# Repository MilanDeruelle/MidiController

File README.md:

# MidiController
Modular Midi Controller/Multiplexer Boards, Software and 3D Printed Case

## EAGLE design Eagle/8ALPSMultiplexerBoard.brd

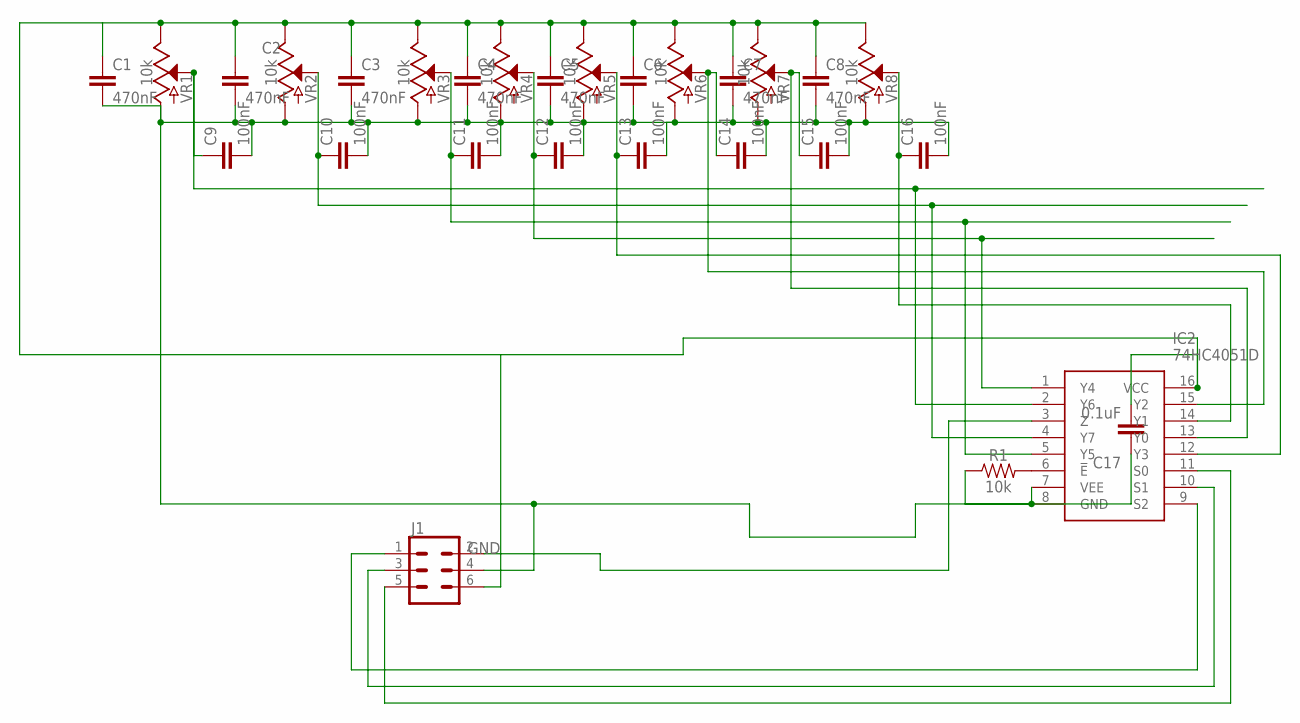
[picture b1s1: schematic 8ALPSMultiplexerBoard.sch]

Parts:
C1, C2, C3, C4, C5, C7, C8: 470nF; C0805
C6: C-EUC0805; C0805
C9, C10, C11, C12, C13, C14, C15, C16: 100nF; C0805
C17: 0.1uF; C0805
IC2: 74HC4051D; SOIC127P600X175-16N
J1: CONN_03X2FEMALE; 2X3
R1: 10k; 0805
VR1, VR2, VR3, VR4, VR5, VR6, VR7, VR8: 10k; POT-PTH-ALPS

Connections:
GND: C1.2, C2.2, C3.2, C4.2, C5.2, C6.2, C7.2, C8.2, C9.2, C10.2, C11.2, C12.2, C13.2, C14.2, C15.2, C16.2, C17.1, IC2.7 (VEE), IC2.8 (GND), J1.4, R1.1, VR1.P$3 (A), VR2.P$3 (A), VR3.P$3 (A), VR4.P$3 (A), VR5.P$3 (A), VR6.P$3 (A), VR7.P$3 (A), VR8.P$3 (A)
unnamed: IC2.6 (!E), R1.2
S0: IC2.11 (S0), J1.5
S1: IC2.10 (S1), J1.3
S2: IC2.9 (S2), J1.1
VCC: C1.1, C2.1, C3.1, C4.1, C5.1, C6.1, C7.1, C8.1, C17.2, IC2.16 (VCC), J1.6, VR1.P$1 (E), VR2.P$1 (E), VR3.P$1 (E), VR4.P$1 (E), VR5.P$1 (E), VR6.P$1 (E), VR7.P$1 (E), VR8.P$1 (E)
Y0: C9.1, IC2.2 (Y6), VR1.P$2 (S)
Y1: C10.1, IC2.4 (Y7), VR2.P$2 (S)
Y2: C11.1, IC2.5 (Y5), VR3.P$2 (S)
Y3: C12.1, IC2.1 (Y4), VR4.P$2 (S)
Y4: C13.1, IC2.12 (Y3), VR5.P$2 (S)
Y5: C14.1, IC2.15 (Y2), VR6.P$2 (S)
Y6: C15.1, IC2.13 (Y0), VR7.P$2 (S)
Y7: C16.1, IC2.14 (Y1), VR8.P$2 (S)
Z: IC2.3 (Z), J1.2

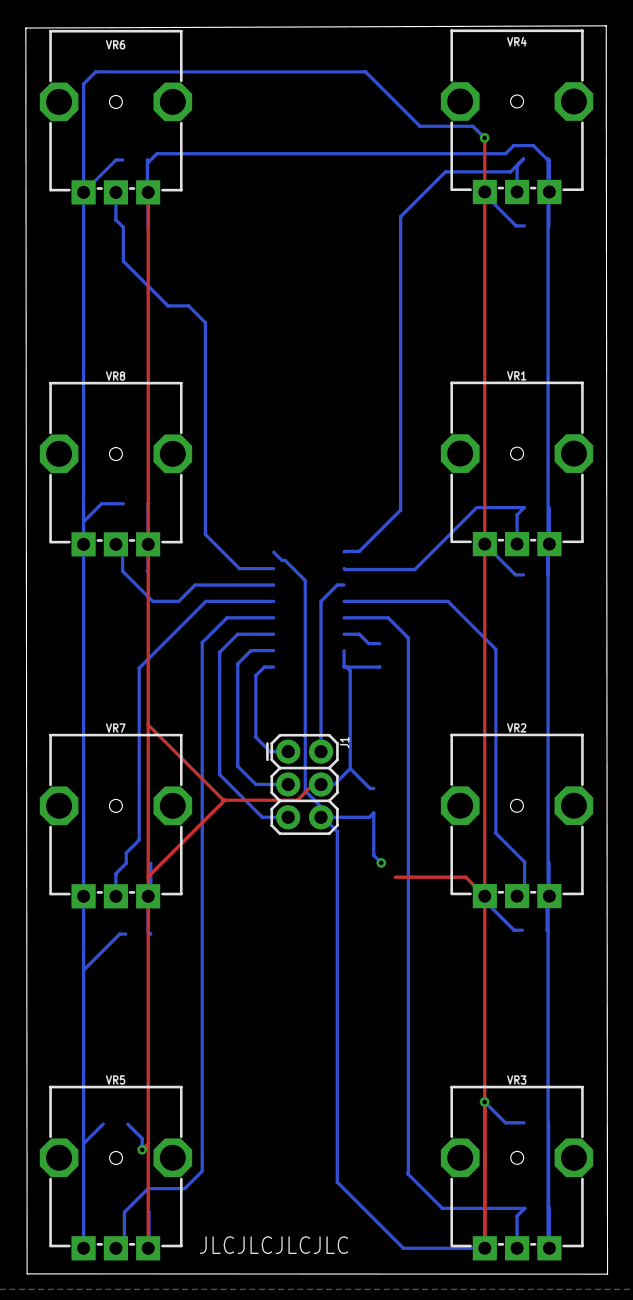
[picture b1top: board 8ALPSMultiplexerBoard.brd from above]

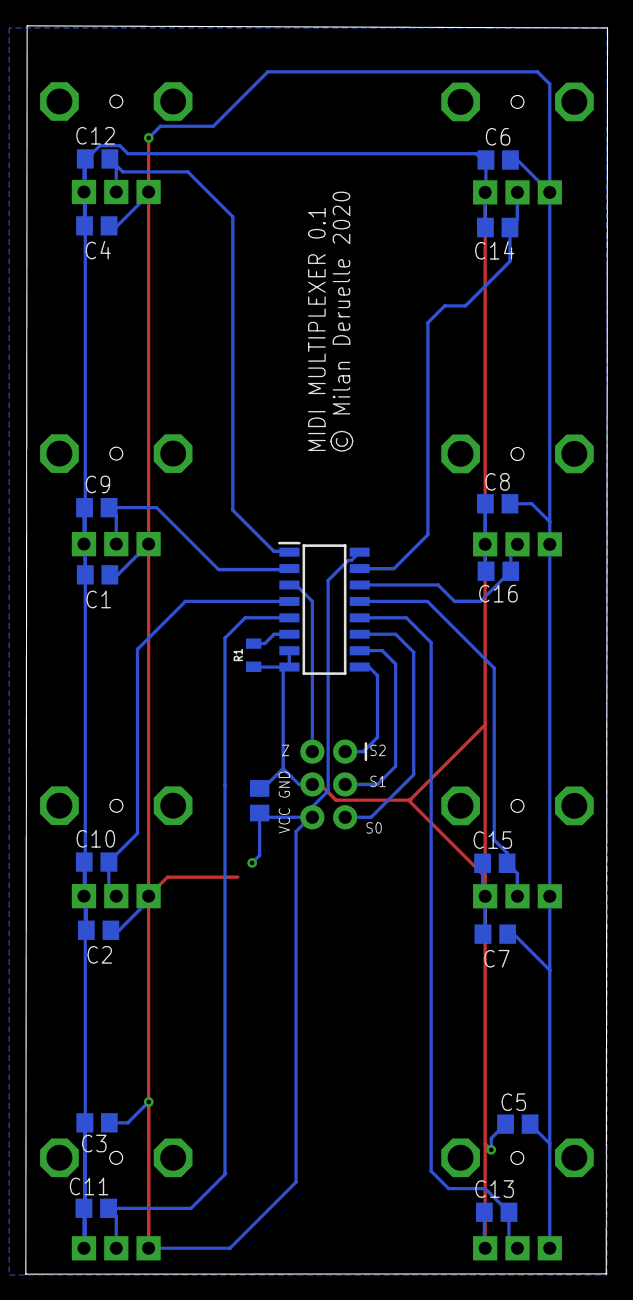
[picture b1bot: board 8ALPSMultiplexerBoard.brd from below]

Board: 2 copper layers, 45.0 x 96.6 mm, 28 parts (19 on the bottom side), 15 nets.

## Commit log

2020-04-29 Version 1.0

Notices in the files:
Eagle/8ALPSMultiplexerBoard.brd:
© Milan Deruelle 2020
parts and their libraries:
SparkFun-Connectors: Licensing: Creative Commons ShareAlike 4.0 International - https://creativecommons.org/licenses/by-sa/4.0
